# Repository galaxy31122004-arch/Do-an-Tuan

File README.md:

# Đồ án 2 — Giám sát nhiệt độ và độ ẩm qua Internet

Thiết kế đã thống nhất: **DHT11 → AT89S52 → OLED SSD1315**; **AT89S52 ↔ ESP32 → Wi-Fi/Internet → nền tảng IoT → dashboard web**.

- Mạch thật; AT89S52 phụ trách đo/hiển thị, ESP32 phụ trách mạng.
- OLED trắng 0,96 inch I²C, hai trang qua nút nhấn.
- Nền tảng có sẵn theo hướng ThingsBoard; dịch vụ cụ thể chưa chốt.
- Dashboard: số đo mới nhất, biểu đồ, lịch sử, lọc thời gian, CSV và cảnh báo ngưỡng.
- Mất mạng vẫn đo tại chỗ; tự kết nối lại, chưa lưu bù.
- Relay (firmware v0.2.0): AT89S52 tự bật tải ≥ 32,0 °C, tắt ≤ 30,0 °C, tắt khi lỗi cảm biến; trạng thái hiện trên OLED và dashboard.

## Tài liệu

- Bản gốc: [Tóm tắt đề tài](documents/sources/de-tai/TÓM%20TẮT%20ĐỀ%20TÀI%20ĐỒ%20ÁN%202.docx).
- Bản cập nhật: [Tóm tắt IoT OLED](documents/sources/de-tai/TÓM%20TẮT%20ĐỀ%20TÀI%20ĐỒ%20ÁN%202%20-%20IoT%20OLED.docx).
- [Cấu trúc tài liệu](documents/de-tai/01-cau-truc-tong-the.md) và [phạm vi đã xác nhận](documents/de-tai/02-yeu-cau-thong-tin.md).

## Workspace

AXON lưu trạng thái tại `.planning/state.json`; bối cảnh, kiến trúc và quy ước tại `.planning/project/`. Planning có repository riêng và lịch sử tự lưu cục bộ. Chưa cấu hình remote.

## Firmware, dashboard và phần cứng

| Thành phần | Tệp / hướng dẫn |
|---|---|
| AT89S52 — đọc DHT11, giờ từ ESP32, OLED, UART | [main.c](firmware/v0.2.0/at89s52/main.c) |
| ESP32 — UART, Wi-Fi, HTTPS, NTP | [main.cpp](firmware/v0.2.0/esp32/src/main.cpp) |
| Build, nạp và giao thức | [Hướng dẫn firmware](docs/firmware.md) |
| Dashboard native để import | [environment-monitor.json](dashboard/environment-monitor.json) |
| Tạo thiết bị, dashboard và alarm rules | [Hướng dẫn nền tảng](dashboard/README.md) |
| Tất cả linh kiện cần lắp/hàn | [BOM.md](hardware/BOM.md) / [BOM.csv](hardware/BOM.csv) |
| Sơ đồ nối dây | [Hình SVG](hardware/wiring.svg) / [Bảng chân chi tiết](hardware/wiring.md) |
| Kế hoạch và nguồn kỹ thuật | [Kế hoạch](docs/implementation-plan.md) / [Nguồn](docs/sources.md) |
| Giá linh kiện và PCB 120.000đ | [Bảng giá](hardware/cost-estimate.md) / [CSV](hardware/cost-estimate.csv) |
| ThingsBoard thật trên máy | [Local demo](dashboard/local/README.md) — http://127.0.0.1:18080 |

## Chạy thử

1. Lắp và kiểm tra nguồn theo tài liệu phần cứng; chưa có PCB sản xuất tự động từ sơ đồ này.
2. Nạp AT89S52 bằng Burn-E với HEX được biên dịch từ đúng mã nguồn, chạy Verify rồi cắm AT89S52 vào mạch. File HEX đã build: `firmware/v0.2.0/at89s52/release/environment-monitor.hex`; bạn tự chạy Verify trên chip bằng Burn-E. Build ESP32 bằng `pio run -d firmware/v0.2.0/esp32 -e esp32c3`.
3. Tạo `firmware/v0.2.0/esp32/include/secrets.h` từ file example; điền Wi-Fi, HTTPS host, device token và root CA. Không đưa credentials lên Git.
4. Tạo device `ENV-MONITOR-01`, import dashboard và cấu hình alarm rules theo hướng dẫn nền tảng.
5. Có thể dùng environment `demo` để phát dữ liệu giả có nhãn trước khi gắn AT89S52.

## Trạng thái kiểm tra

- ESP32 live và demo đã build trên máy phát triển; kiểm thử UART/calendar native và kiểm tra cấu trúc dashboard/BOM có trong `tests/`.
- Không dùng RTC/pin dự phòng. ESP32 lấy giờ NTP, gửi cho AT89S52 hiển thị UTC+7; khởi động chưa có mạng báo chưa đồng bộ.
- Đã chọn module TXS0108E: bốn kênh I²C/UART, OE từ GPIO6. Xem bảng chân trước khi lắp.
- AT89S52 đã build bằng SDCC trong giới hạn Flash/RAM; HEX và báo cáo tại `firmware/v0.2.0/at89s52/release/`. Người dùng tự Verify bằng Burn-E; chưa kiểm thử mạch thật.
- Dashboard đã import và kiểm tra trên ThingsBoard CE cục bộ tại `http://127.0.0.1:18080`; dữ liệu có nhãn giả lập. Chưa kết nối mạch thật hoặc triển khai Internet. Xem [cách chạy/dừng demo](dashboard/local/README.md).

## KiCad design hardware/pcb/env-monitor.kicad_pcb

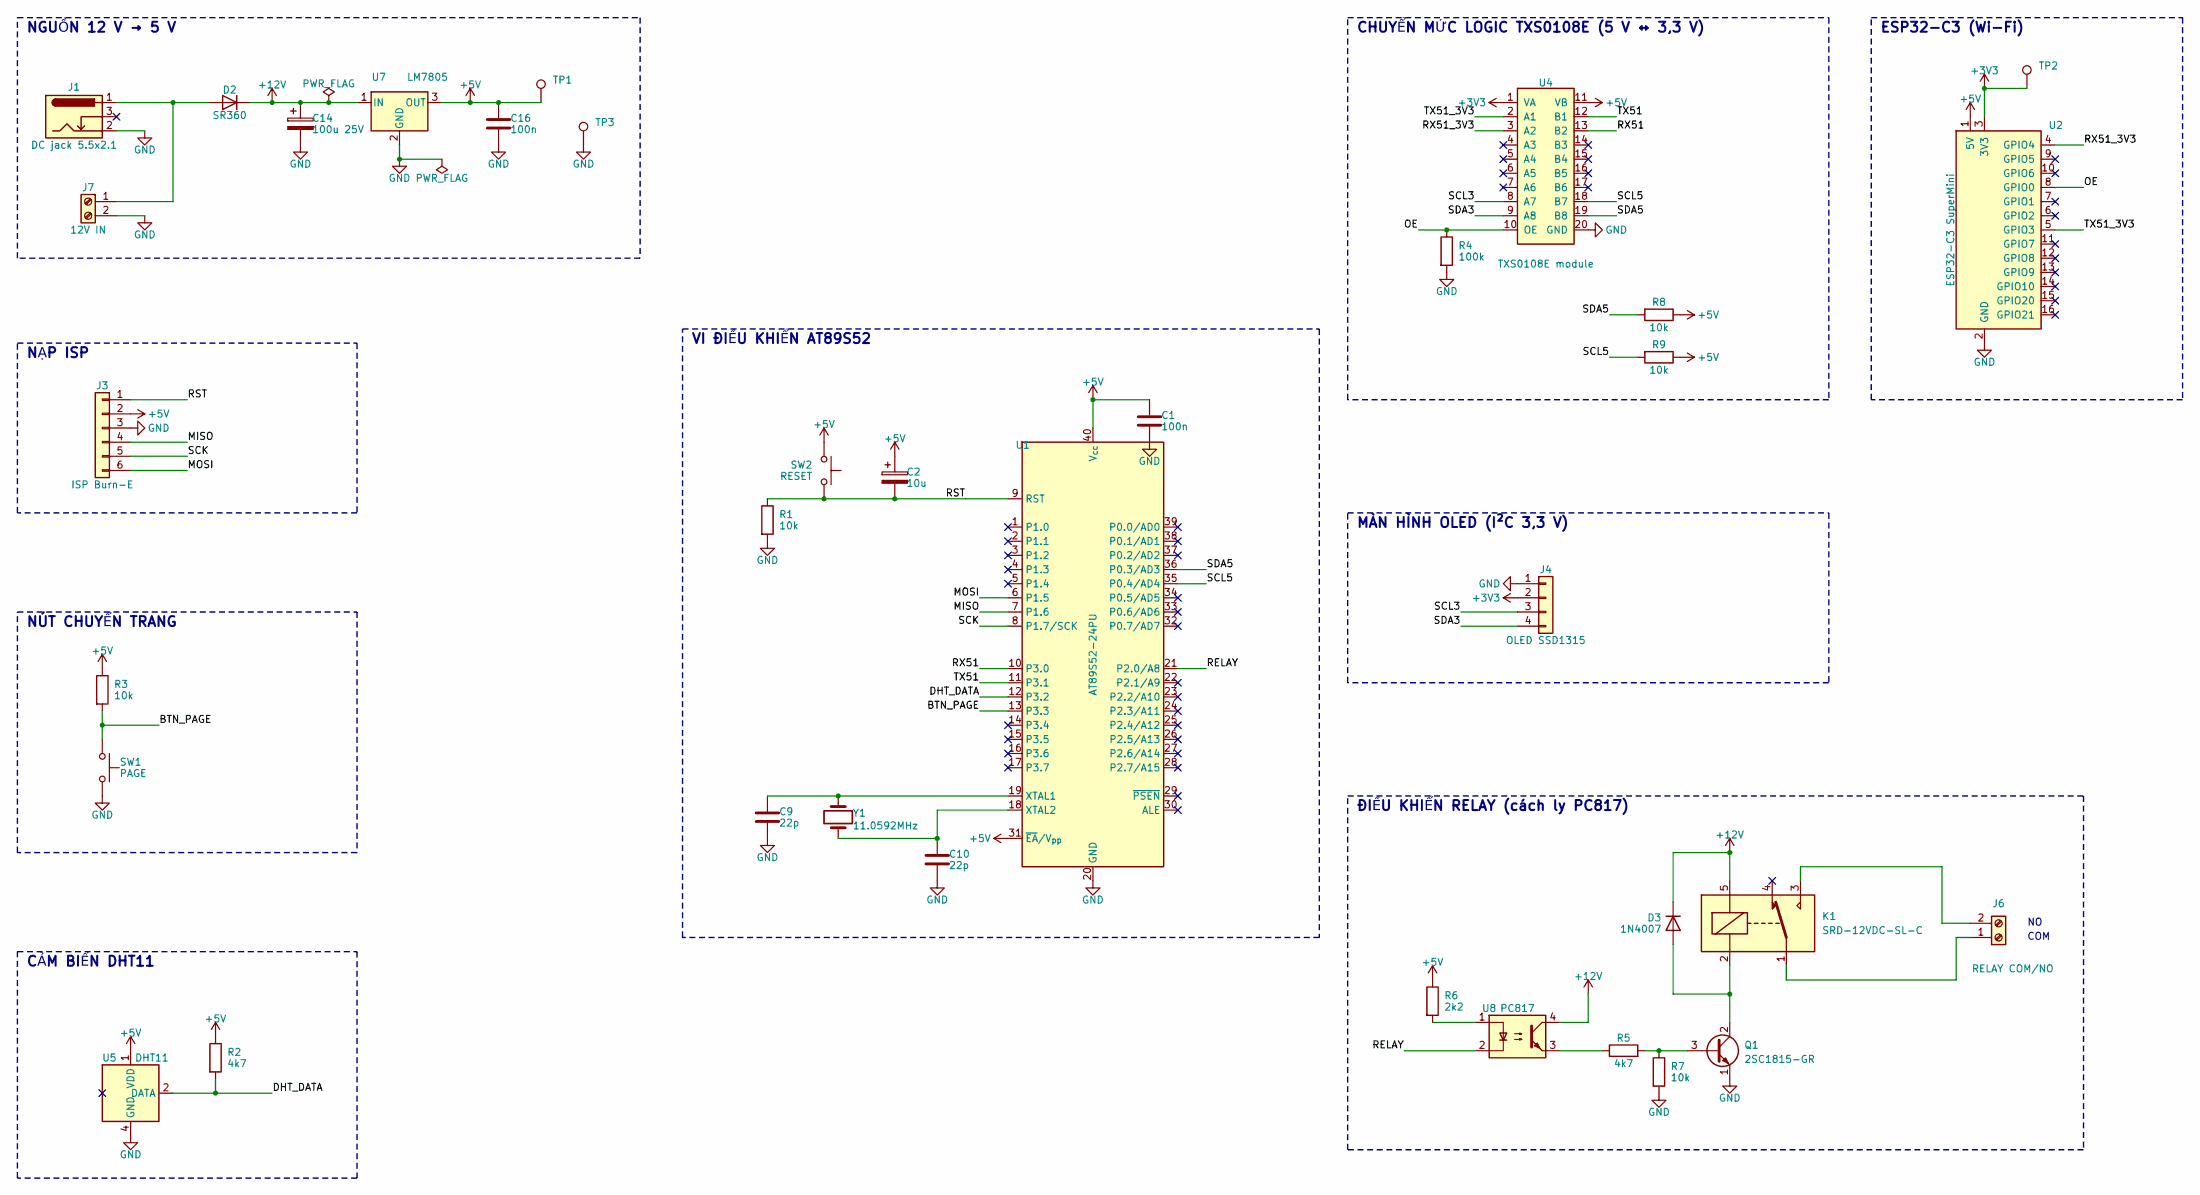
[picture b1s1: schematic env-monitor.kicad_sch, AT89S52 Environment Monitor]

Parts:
C1: 100n; C_Disc_D3.0mm_W1.6mm_P2.50mm
C2: 10u; CP_Radial_D5.0mm_P2.00mm
C9, C10: 22p; C_Disc_D3.0mm_W1.6mm_P2.50mm
C14: 100u 25V; CP_Radial_D6.3mm_P2.50mm
C16: 100n; C_Disc_D5.0mm_W2.5mm_P5.00mm
D2: SR360; D_DO-201AD_P15.24mm_Horizontal
D3: 1N4007; D_DO-41_SOD81_P10.16mm_Horizontal
J1: DC jack 5.5x2.1; BarrelJack_Horizontal
J3: ISP Burn-E; PinHeader_1x06_P2.54mm_Vertical
J4: OLED SSD1315; OLED_0.96_I2C_Module
J6: RELAY COM/NO; TerminalBlock_Phoenix_MKDS-1,5-2-5.08_1x02_P5.08mm_Horizont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
J7: 12V IN; TerminalBlock_Phoenix_MKDS-1,5-2-5.08_1x02_P5.08mm_Horizont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
K1: SRD-12VDC-SL-C; Relay_SPDT_SANYOU_SRD_Series_Form_C
Q1: 2SC1815-GR; TO-92_Inline_Wide
R1, R3, R8, R9: 10k; R_Axial_DIN0207_L6.3mm_D2.5mm_P7.62mm_Horizontal
R2, R5: 4k7; R_Axial_DIN0207_L6.3mm_D2.5mm_P10.16mm_Horizontal
R4: 100k; R_Axial_DIN0207_L6.3mm_D2.5mm_P10.16mm_Horizontal
R6: 2k2; R_Axial_DIN0207_L6.3mm_D2.5mm_P10.16mm_Horizontal
R7: 10k; R_Axial_DIN0207_L6.3mm_D2.5mm_P10.16mm_Horizontal
SW1: PAGE; SW_PUSH_6mm
SW2: RESET; SW_PUSH_6mm
TP1: +5V; TestPoint_THTPad_D1.5mm_Drill0.7mm
TP2: +3V3; TestPoint_THTPad_D1.5mm_Drill0.7mm
TP3: GND; TestPoint_THTPad_D1.5mm_Drill0.7mm
U1: AT89S52-24PU; DIP-40_W15.24mm_Socket
U2: ESP32-C3 SuperMini; ESP32-C3_SuperMini
U4: TXS0108E module; TXS0108E_Module
U5: DHT11; Aosong_DHT11_5.5x12.0_P2.54mm
U7: LM7805; TO-220-3_Horizontal_TabDown
U8: PC817; DIP-4_W7.62mm
Y1: 11.0592MHz; Crystal_HC49-4H_Vertical

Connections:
+3V3: J4.2, TP2.1 (1_1), U2.3 (3V3), U4.1 (VA)
+5V: C1.1, C2.1, C16.1, J3.2, R2.1, R3.1, R6.1, R8.1, R9.1, SW2.1, TP1.1 (1_1), U1.31 (~EA/V_{pp}), U1.40 (V_{cc}), U2.1 (5V), U4.11 (VB), U5.1 (VDD), U7.3 (OUT)
+12V: C14.1, D2.1 (K), D3.1 (K), K1.5, U7.1 (IN), U8.4
/BTN_PAGE: R3.2, SW1.1, U1.13 (P3.3)
/DHT_DATA: R2.2, U1.12 (P3.2), U5.2 (DATA)
/MISO: J3.4, U1.7 (P1.6)
/MOSI: J3.6, U1.6 (P1.5)
/OE: R4.1, U2.8 (GPIO0), U4.10 (OE)
/RELAY: U1.21 (P2.0/A8), U8.2
/RST: C2.2, J3.1, R1.1, SW2.2, U1.9 (RST)
/RX51: U1.10 (P3.0), U4.13 (B2)
/RX51_3V3: U2.4 (GPIO4), U4.3 (A2)
/SCK: J3.5, U1.8 (P1.7/SCK)
/SCL3: J4.3, U4.8 (A7)
/SCL5: R9.2, U1.35 (P0.4/AD4), U4.18 (B7)
/SDA3: J4.4, U4.9 (A8)
/SDA5: R8.2, U1.36 (P0.3/AD3), U4.19 (B8)
/TX51: U1.11 (P3.1), U4.12 (B1)
/TX51_3V3: U2.5 (GPIO3), U4.2 (A1)
GND: C1.2, C9.2, C10.2, C14.2, C16.2, J1.2, J3.3, J4.1, J7.2, Q1.1 (E), R1.2, R4.2, R7.2, SW1.2, TP3.1 (1_1), U1.20 (GND), U2.2 (GND), U4.20 (GND), U5.4 (GND), U7.2 (GND)
unnamed: D2.2 (A), J1.1, J7.1
unnamed: D3.2 (A), K1.2, Q1.2 (C)
unnamed: J6.1, K1.1
unnamed: J6.2, K1.3
unnamed: Q1.3 (B), R5.2, R7.1
unnamed: R5.1, U8.3
unnamed: R6.2, U8.1
unnamed: C9.1, U1.19 (XTAL1), Y1.1
unnamed: C10.1, U1.18 (XTAL2), Y1.2

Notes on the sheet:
NGUỒN 12 V → 5 V
NẠP ISP
NÚT CHUYỂN TRANG
CẢM BIẾN DHT11
VI ĐIỀU KHIỂN AT89S52
CHUYỂN MỨC LOGIC TXS0108E (5 V ↔ 3,3 V)
ESP32-C3 (Wi-Fi)
MÀN HÌNH OLED (I²C 3,3 V)
ĐIỀU KHIỂN RELAY (cách ly PC817)
COM

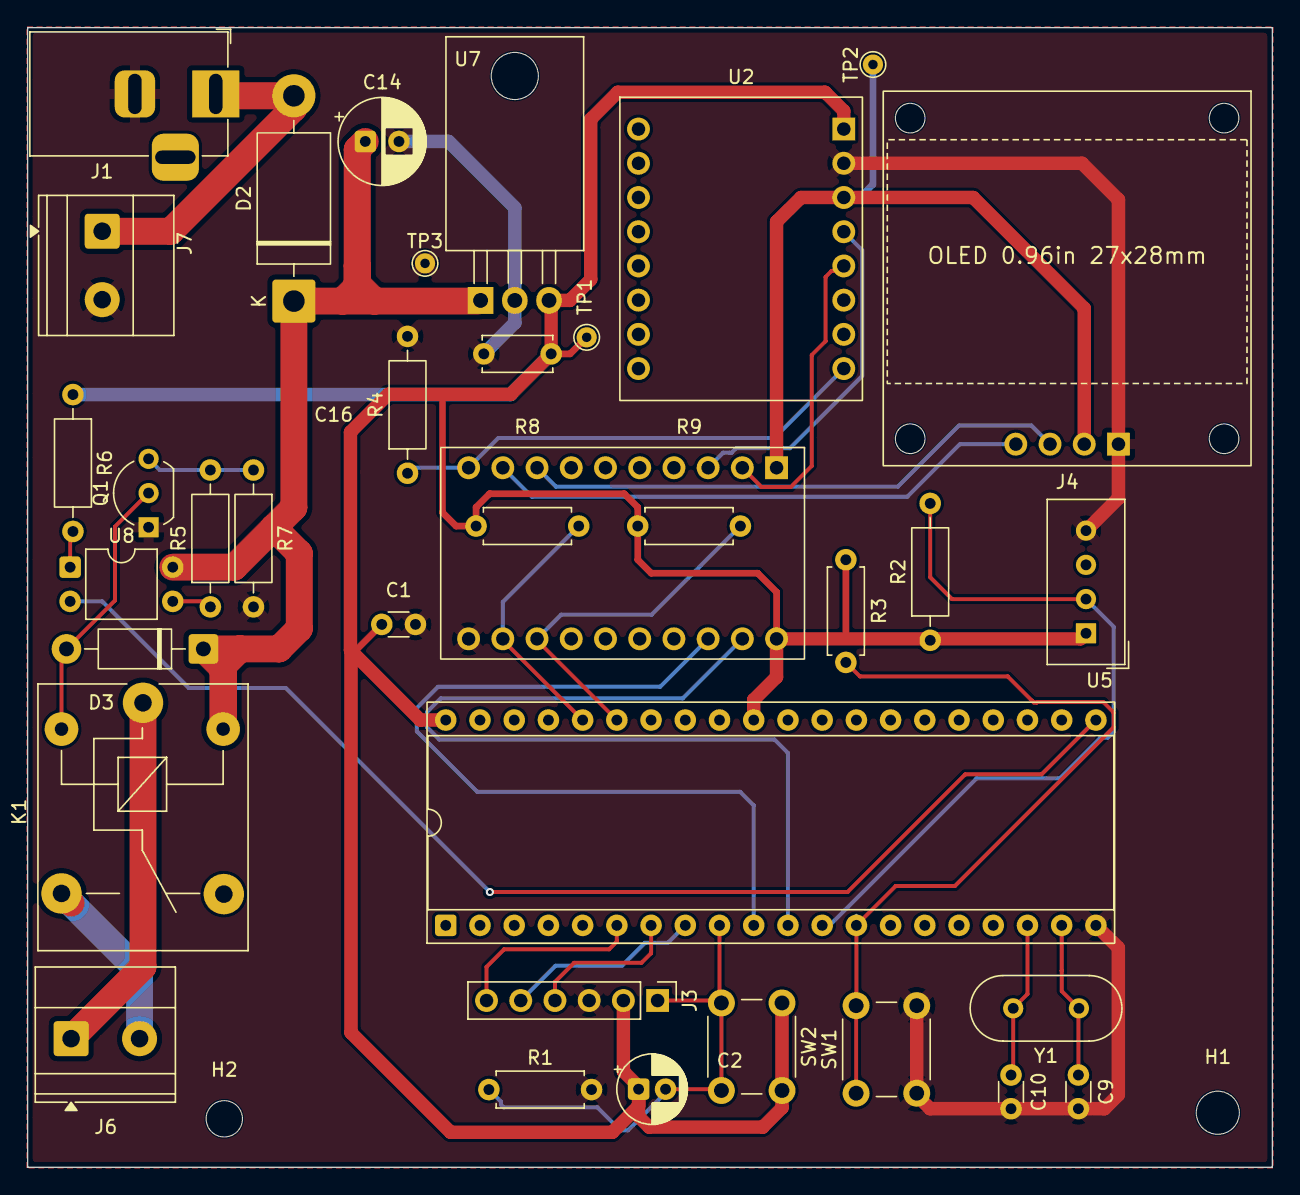
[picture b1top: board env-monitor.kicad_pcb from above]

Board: 2 copper layers, 92.4 x 84.6 mm, 38 parts (0 on the bottom side), 29 nets.

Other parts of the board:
H1: M3; MountingHole_3.2mm_M3
H2: M2.5; MountingHole_2.7mm_M2.5

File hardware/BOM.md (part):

# Danh sách đầy đủ linh kiện trên mạch

Phương án lắp: AT89S52 dùng IC rời có đế; ESP32, OLED và TXS0108E là module cắm header. Mọi đế/header trong bảng đều được hàn lên PCB. IC/module cắm vào sau khi kiểm tra nguồn. Không cộng lại những linh kiện đã có sẵn bên trong module.

Giá tham khảo ngày **01/11/2026**, đơn vị VND. Bảng đầu ghi **đơn giá một linh kiện và thành tiền theo số lượng lắp**; bảng mua theo gói ở dưới ghi tiền cần trả khi mua mới. Đơn giá trở/LED/nút/header được quy đổi từ gói/thanh, không phải xác nhận shop bán lẻ từng chiếc.

| Ký hiệu | SL lắp | Linh kiện | Đơn giá/chi tiết | Thành tiền lắp | Kiểu lắp | Vị trí / lưu ý |
|---|---:|---|---:|---:|---|---|
| U1 | 1 | [AT89S52-24PU](https://chotroihn.vn/at89s52-24pu-dip40) | 27.000đ | 27.000đ | DIP-40 | Bộ xử lý đo/hiển thị; nguồn 5 V. Giá: 1 IC DIP40; RSCH-20261101-0011; shop khác có giá 79.000đ |
| U2 | 1 | [ESP32-C3 SuperMini](https://icdayroi.com/kit-phat-trien-wifi-bluetooth-esp32-c3-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 | 75.000đ | 75.000đ | 16 chân, 2 hàng 1x8 | Board ESP32-C3 SuperMini; xác minh footprint và nhãn GPIO trước khi làm PCB. Giá: 1 board; RSCH-20261101-0009 |
| U4 | 1 | [Module TXS0108E 8 kênh](https://icdayroi.com/txs0108e-8-kenh-chuyen-muc-logic-1-8v-3-3v-5v) | 15.000đ | 15.000đ | Module 2 hàng, đối chiếu footprint | A=3,3 V; B=5 V; bốn kênh I²C/UART; OE từ ESP32 GPIO0. Giá: 1 module; RSCH-20261101-0009 |
| U5 | 1 | [DHT11 cảm biến rời](https://chotroihn.vn/cam-bien-nhiet-do-do-am-dht11) | 25.000đ | 25.000đ | 4 chân | VCC/DATA/NC/GND; không nhầm pin module 3 chân. Giá: 1 cảm biến; RSCH-20261101-0009 |
| U6 | 1 | [OLED trắng 0,96 inch SSD1315 I²C 128x64](https://hshop.vn/lcd-oled-trang-0-96-inch-i2c) | 65.000đ | 65.000đ | Module 4 chân | Module Hshop đã chọn; cấp 3,3 V, kiểm tra thứ tự chân in trên module. Giá: 1 màn hình; RSCH-20261101-0009 |
| Y1 | 1 | [Thạch anh 11,0592 MHz](https://icdayroi.com/thach-anh-11-0592mhz-hc49-dip) | 1.500đ | 1.500đ | HC-49S | Dao động 11,0592 MHz cho UART 9600; đối chiếu điện dung tải. Giá: 1 thạch anh; RSCH-20261101-0011 |
| R1,R3,R7,R8,R9 | 5 | [10 kΩ 1% 0,25 W](https://chotroihn.vn/tro-vach-1-4w-1-50c) | 120đ | 600đ | Axial THT | R1 kéo RST chân 9 xuống GND; R3 kéo nút trang lên 5 V; R7 base-emitter Q1 giữ Q1 tắt; R8/R9 kéo SDA/SCL (P0.3/P0.4, cực máng hở) lên 5 V. Giá: Mua gói 50, dùng 5; trang báo hết hàng biến thể này; cần xác nhận nguồn khác |
| R6 | 1 | 2,2 kΩ 0,25 W | Chưa xác nhận | Chưa xác nhận | Axial THT | Hạn dòng LED PC817 (~1,5 mA khi P2.0 kéo xuống). Giá: Chưa khảo sát giá |
| U8 | 1 | PC817 opto | Chưa xác nhận | Chưa xác nhận | DIP-4 | LED phía 5 V: +5 V-R6-anode, cathode-P2.0; transistor phía 12 V: C lên +12V, E qua R5 vào base Q1. Giá: Chưa khảo sát giá |
| R2 | 1 | [4,7 kΩ 1% 0,25 W](https://chotroihn.vn/tro-vach-1-4w-1-50c) | 120đ | 120đ | Axial THT | Kéo DATA DHT11 lên 5 V. Giá: Mua gói 50, dùng 1 |
| R4 | 1 | [100 kΩ 1% 0,25 W](https://chotroihn.vn/tro-vach-1-4w-1-50c) | 120đ | 120đ | Axial THT | Kéo OE TXS0108E xuống GND khi ESP32 khởi động; bỏ pull-up OE trên module nếu có. Giá: Mua gói 50, dùng 1; trang báo hết hàng biến thể này; cần xác nhận nguồn khác |
| R5 | 1 | 4,7 kΩ 0,25 W | Chưa xác nhận | Chưa xác nhận | Axial THT | Từ emitter PC817 (phía 12 V) vào base Q1. Giá: Chưa khảo sát giá; có thể lấy từ gói 4 |
| C1,C16 | 2 | [100 nF X7R ≥16 V](https://chotroihn.vn/tu-gom-vang-50v) | 500đ | 1.000đ | THT 2,54 mm | VCC AT89S52 và đầu ra LM7805; đặt sát chân. Giá: Giá biến thể 0.1uF/104; đối chiếu điện môi X7R theo BOM trước khi mua |
| C14 | 1 | 100 µF ≥25 V | Chưa xác nhận | Chưa xác nhận | Tụ hóa radial | Đầu vào LM7805 sau D2; đúng cực. Giá: Chưa khảo sát giá |
| C9,C10 | 2 | [22 pF C0G/NP0 ≥25 V](https://chotroihn.vn/tu-gom-vang-50v) | 500đ | 1.000đ | Tụ gốm THT | Hai tụ Y1; giá trị khởi đầu, đối chiếu CL thạch anh trước khi chốt PCB. Giá: Giá biến thể 22P; xác nhận C0G/NP0 và tải thạch anh trước khi mua |
| C2 | 1 | [10 µF ≥10 V](https://chotroihn.vn/tu-hoa-16v) | 1.000đ | 1.000đ | Tụ hóa radial | C2 reset: cực + lên 5 V, cực - vào RST chân 9. Giá: C2 reset; kiểm tra cực tính |
| U7 | 1 | LM7805 ổn áp 5 V 1,5 A | Chưa xác nhận | Chưa xác nhận | TO-220 nằm ngang, vít xuống PCB | Tab = GND: vít M3 xuống vùng đồng GND hai mặt; với 12 V tỏa ~1,6 W, cần vùng đồng lớn hoặc tản phụ. Giá: Chưa khảo sát giá |
| D2 | 1 | SR360 Schottky 3 A 60 V | Chưa xác nhận | Chưa xác nhận | DO-201AD | Chống cắm ngược cực nguồn 12 V, sụt áp ~0,5 V; nối tiếp trước LM7805. Giá: Chưa khảo sát giá |
| SW1,SW2 | 2 | [Nút nhấn thường hở](https://chotroihn.vn/bo-10-nut-nhan-4-chan) | 500đ | 1.000đ | Tactile 6x6 mm | SW1 đổi trang; SW2 reset AT89S52. Giá: Mua gói 10, dùng 2 |
| J1 | 1 | Jack DC 5,5x2,1 mm hàn mạch | Chưa xác nhận | Chưa xác nhận | DC-005, 3 chân | Tâm dương; chân switch để trống. Giá: Chưa khảo sát giá |
| J7 | 1 | Domino 2 chân 5,08 mm | Chưa xác nhận | Chưa xác nhận | Pitch 5,08 mm | Đầu vào 12 V song song jack J1: chân 1 (+), chân 2 GND; chỉ cấp một nguồn. Giá: Chưa khảo sát giá |
| J2A,J2B | 2 | [Header cái 1x8](https://chotroihn.vn/jump-cai-don-1-40p-2-54) | 400đ | 800đ | Pitch 2,54 mm | Đế cắm ESP32; hai hàng cách 15,24 mm (0,6″) theo thông số board. Giá: 2 thanh 40 chân để cắt 8+8+4+10+10; chừa hao hụt khi cắt |
| J4 | 1 | [Header cái 1x4](https://chotroihn.vn/jump-cai-don-1-40p-2-54) | 200đ | 200đ | Pitch 2,54 mm | Đế cắm OLED. Giá: 2 thanh 40 chân để cắt 8+8+4+10+10; chừa hao hụt khi cắt |
| J3 | 1 | [Header ISP AT89S52 1x6](https://chotroihn.vn/jump-duc-don-1x40p-2-54) | 300đ | 300đ | Pitch 2,54 mm | RST/VCC/GND/MISO/SCK/MOSI; nạp chính bằng Burn-E ngoài mạch. Giá: 1 thanh 40 chân, dùng 6 chân ISP AT89S52; giả định chân đực module đi kèm module |
| J5A,J5B | 2 | [Header cái 1x10 cho module TXS0108E](https://chotroihn.vn/jump-cai-don-1-40p-2-54) | 500đ | 1.000đ | Pitch 2,54 mm, xác minh hàng mua | Hàn đế module; chỉnh số chân/footprint nếu module thực tế khác. Giá: 2 thanh 40 chân để cắt 8+8+4+10+10; chừa hao hụt khi cắt |
| J6 | 1 | Domino 2 chân 5,08 mm | Chưa xác nhận | Chưa xác nhận | Pitch 5,08 mm | COM/NO của relay K1 (NC bỏ trống); tải có điện khi relay bật (≥32 °C); chỉ tải điện áp thấp. Giá: Chưa khảo sát giá |
| K1 | 1 | Relay SRD-12VDC-SL-C | Chưa xác nhận | Chưa xác nhận | Hàn PCB, SPDT | Cuộn 12 V ~30 mA lấy từ +12V sau SR360; chân 2/5 cuộn, 1 COM, 3 NO ra J6, 4 NC bỏ trống. Giá: Chưa khảo sát giá |
| Q1 | 1 | 2SC1815-GR NPN | Chưa xác nhận | Chưa xác nhận | TO-92 E-C-B | Đóng phía GND cuộn relay, base từ emitter PC817 qua R5. Giá: Chưa khảo sát giá |
| D3 | 1 | 1N4007 | Chưa xác nhận | Chưa xác nhận | DO-41 | Điốt dập xung ngược song song cuộn relay. Giá: Chưa khảo sát giá |
| SK1 | 1 | [Đế IC DIP-40](https://chotroihn.vn/de-ic) | 1.500đ | 1.500đ | Wide 15,24 mm | Đế AT89S52, hàn đế rồi cắm IC. Giá: Biến thể 40 chân; xác nhận loại rộng cho AT89S52 DIP40 |
| TP1,TP2,TP3 | 3 | Test point vòng dây | 0đ | 0đ | THT | Đo 5 V / 3,3 V / GND. Giá: Tận dụng chân/dây cắt thừa của header đã tính; không mua thêm |

**Tổng số chi tiết trong bảng:** 42 (bao gồm IC/module/đế; không gồm PCB và vật tư ngoài mạch).

**Giá trị linh kiện dùng trên một mạch: 217.140đ, chưa gồm mục chưa có giá.**

## Tiền mua thực tế theo gói/thanh

| Mục | Số đơn vị/gói mua | Giá mỗi đơn vị/gói | Thành tiền mua | Quy cách / ghi chú |
|---|---:|---:|---:|---|
| [U1: AT89S52 DIP-40](https://chotroihn.vn/at89s52-24pu-dip40) | 1 | 27.000đ | 27.000đ | 1 IC DIP40; RSCH-20261101-0011; shop khác có giá 79.000đ |
| [U2: ESP32-C3 SuperMini 4MB](https://icdayroi.com/kit-phat-trien-wifi-bluetooth-esp32-c3-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 | 1 | 75.000đ | 75.000đ | 1 board; RSCH-20261101-0009 |
| [U4: Module TXS0108E](https://icdayroi.com/txs0108e-8-kenh-chuyen-muc-logic-1-8v-3-3v-5v) | 1 | 15.000đ | 15.000đ | 1 module; RSCH-20261101-0009 |
| [U5: DHT11 rời 4 chân](https://chotroihn.vn/cam-bien-nhiet-do-do-am-dht11) | 1 | 25.000đ | 25.000đ | 1 cảm biến; RSCH-20261101-0009 |
| [U6: OLED SSD1315 0,96 inch](https://hshop.vn/lcd-oled-trang-0-96-inch-i2c) | 1 | 65.000đ | 65.000đ | 1 màn hình; RSCH-20261101-0009 |
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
